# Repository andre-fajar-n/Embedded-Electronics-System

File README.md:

# Embedded Electronics System Lecture
This repo contains project - project about Embedded Electronics System Lecture when I was in college

## List Contents
### 1. [Circuit Design of AT89C51 and ATMega16](https://github.com/andre-fajar-n/embedded-electronics-system/tree/master/circuit_design)

### 2. [Firmware using Assembly Language](https://github.com/andre-fajar-n/embedded-electronics-system/tree/master/assembly_language)
In this language, there are 3 projects, such as: </br>
a. Showing text in LCD 16x2</br>
b. Automatic Water Reservoir</br>
c. Control Servo</br>

### 3. [Firmware using Bascom Language](https://github.com/andre-fajar-n/embedded-electronics-system/tree/master/bascom_language)
In this language, there are 2 projects, such as: </br>
a. Showing Counter in LCD 16x2</br>
b. Reading the tilt of device from MPU6050 and send Message to a phone number using SIM800L</br>

### 4. [Final Project for this lecture](https://github.com/andre-fajar-n/embedded-electronics-system/tree/master/pulse_position_modulation)
The purpose of final project was sent the signal from one microcontroller to another microcontroller by **PPM (Pulse Position Modulation)** method. The number of signal that was sent is 8 signals. The **sender** used **ATMega16** and the **receiver** used **Arduino Mega** To send the signal, I used infrared LED. And to receive the signal, I used photodiode.

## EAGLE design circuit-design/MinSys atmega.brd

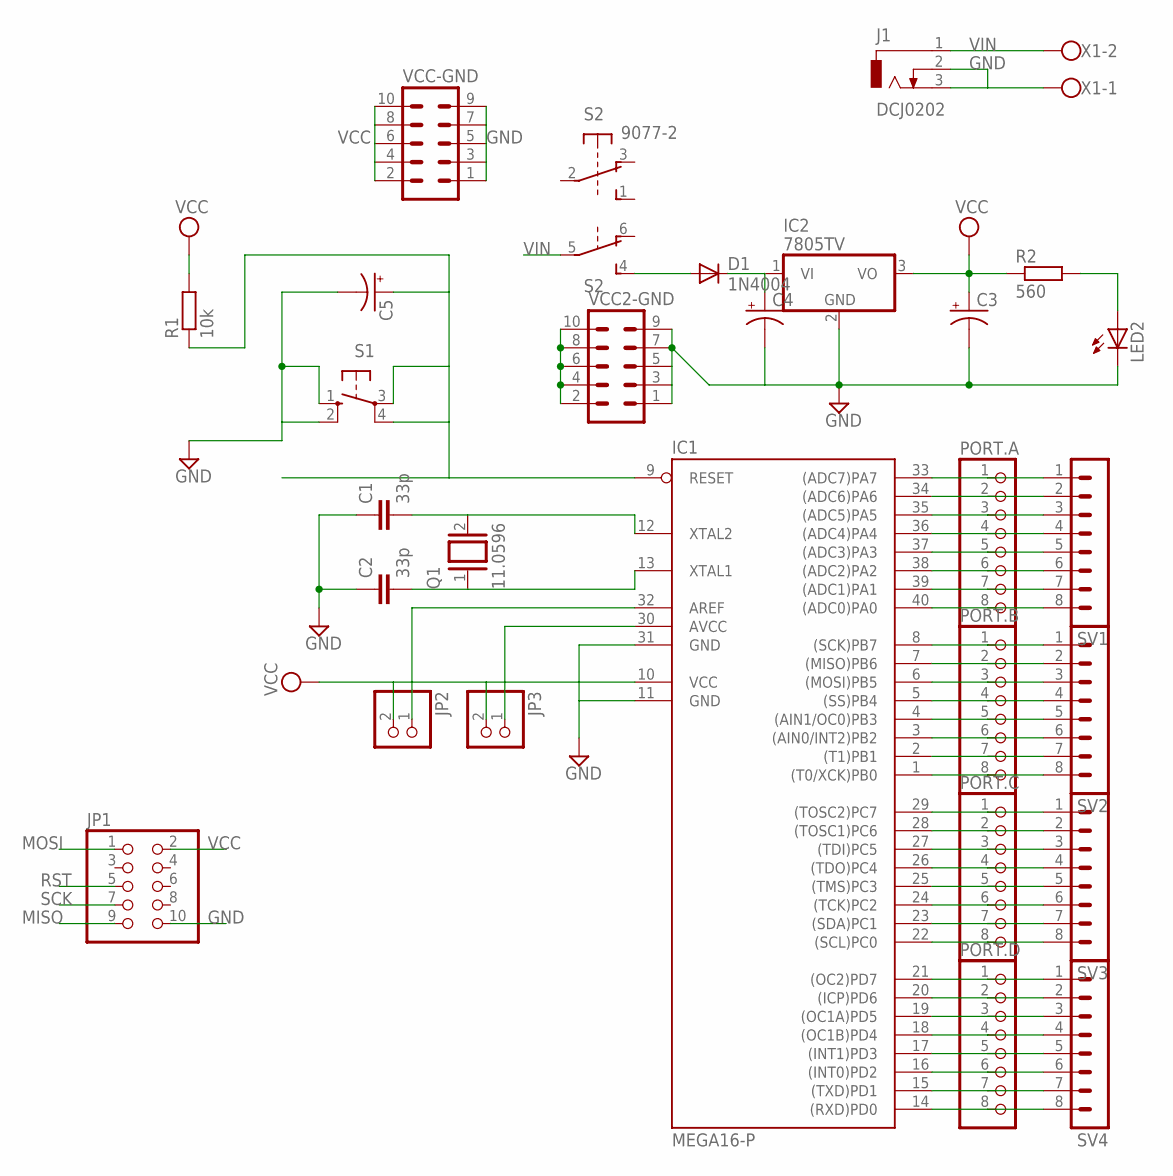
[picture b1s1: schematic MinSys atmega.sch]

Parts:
C1, C2: 33p; C2.5-3
C3, C4: CPOL-USE2,5-6E; E2,5-6E
C5: CPOL-USE2.5-6; E2,5-6
D1: 1N4004; DO41-10
IC1: MEGA16-P; DIL40
IC2: 7805TV; TO220V
J1: DCJ0202
JP1: PINHD-2X5; 2X05
JP2, JP3: PINHD-1X2; 1X02
LED2: LED3MM
PORT.A, PORT.B, PORT.C, PORT.D: PINHD-1X8; 1X08
Q1: 11.0596; QS
R1: 10k; 0207/10
R2: 560; 0207/10
S1: 10-XX; B3F-10XX
S2: 9077-2
SV1, SV2, SV3, SV4: MA08-1
VCC2-GND: MA05-2
VCC-GND: MA05-2
X1: W237-102

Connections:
GND: C1.1, C2.1, C3.-, C4.-, C5.-, IC1.11 (GND), IC1.31 (GND), IC2.2 (GND), J1.2, J1.3, JP1.10, LED2.K (C), S1.1 (S), S1.2 (S1), VCC2-GND.1, VCC2-GND.3, VCC2-GND.5, VCC2-GND.7, VCC2-GND.9, VCC-GND.1, VCC-GND.3, VCC-GND.5, VCC-GND.7, VCC-GND.9, X1.1
MISO: IC1.7 ((MISO)PB6), JP1.9, PORT.B.2, SV2.2
MOSI: IC1.6 ((MOSI)PB5), JP1.1, PORT.B.3, SV2.3
unnamed: IC1.33 ((ADC7)PA7), PORT.A.1, SV1.1
unnamed: D1.A, S2.4 (S)
unnamed: IC1.34 ((ADC6)PA6), PORT.A.2, SV1.2
unnamed: IC1.32 (AREF), JP2.1
unnamed: IC1.30 (AVCC), JP3.1
unnamed: C1.2, IC1.12 (XTAL2), Q1.2
unnamed: C2.2, IC1.13 (XTAL1), Q1.1
unnamed: C4.+, D1.C, IC2.1 (VI)
unnamed: LED2.A, R2.2
P02: IC1.35 ((ADC5)PA5), PORT.A.3, SV1.3
P03: IC1.36 ((ADC4)PA4), PORT.A.4, SV1.4
P04: IC1.37 ((ADC3)PA3), PORT.A.5, SV1.5
P05: IC1.38 ((ADC2)PA2), PORT.A.6, SV1.6
P06: IC1.39 ((ADC1)PA1), PORT.A.7, SV1.7
P07: IC1.40 ((ADC0)PA0), PORT.A.8, SV1.8
P10: IC1.14 ((RXD)PD0), PORT.D.8, SV4.8
P11: IC1.15 ((TXD)PD1), PORT.D.7, SV4.7
P12: IC1.16 ((INT0)PD2), PORT.D.6, SV4.6
P13: IC1.17 ((INT1)PD3), PORT.D.5, SV4.5
P14: IC1.18 ((OC1B)PD4), PORT.D.4, SV4.4
P15: IC1.19 ((OC1A)PD5), PORT.D.3, SV4.3
P16: IC1.20 ((ICP)PD6), PORT.D.2, SV4.2
P17: IC1.21 ((OC2)PD7), PORT.D.1, SV4.1
P23: IC1.5 ((SS)PB4), PORT.B.4, SV2.4
P24: IC1.4 ((AIN1/OC0)PB3), PORT.B.5, SV2.5
P25: IC1.3 ((AIN0/INT2)PB2), PORT.B.6, SV2.6
P26: IC1.2 ((T1)PB1), PORT.B.7, SV2.7
P27: IC1.1 ((T0/XCK)PB0), PORT.B.8, SV2.8
P30: IC1.22 ((SCL)PC0), PORT.C.8, SV3.8
P31: IC1.23 ((SDA)PC1), PORT.C.7, SV3.7
P32: IC1.24 ((TCK)PC2), PORT.C.6, SV3.6
P33: IC1.25 ((TMS)PC3), PORT.C.5, SV3.5
P34: IC1.26 ((TDO)PC4), PORT.C.4, SV3.4
P35: IC1.27 ((TDI)PC5), PORT.C.3, SV3.3
P36: IC1.28 ((TOSC1)PC6), PORT.C.2, SV3.2
P37: IC1.29 ((TOSC2)PC7), PORT.C.1, SV3.1
RST: C5.+, IC1.9 (RESET), JP1.5, R1.1, S1.3, S1.4 (P1)
SCK: IC1.8 ((SCK)PB7), JP1.7, PORT.B.1, SV2.1
VCC: C3.+, IC1.10 (VCC), IC2.3 (VO), JP1.2, JP2.2, JP3.2, R1.2, R2.1, VCC2-GND.2, VCC2-GND.4, VCC2-GND.6, VCC2-GND.8, VCC2-GND.10, VCC-GND.2, VCC-GND.4, VCC-GND.6, VCC-GND.8, VCC-GND.10
VIN: J1.1, S2.5, X1.2

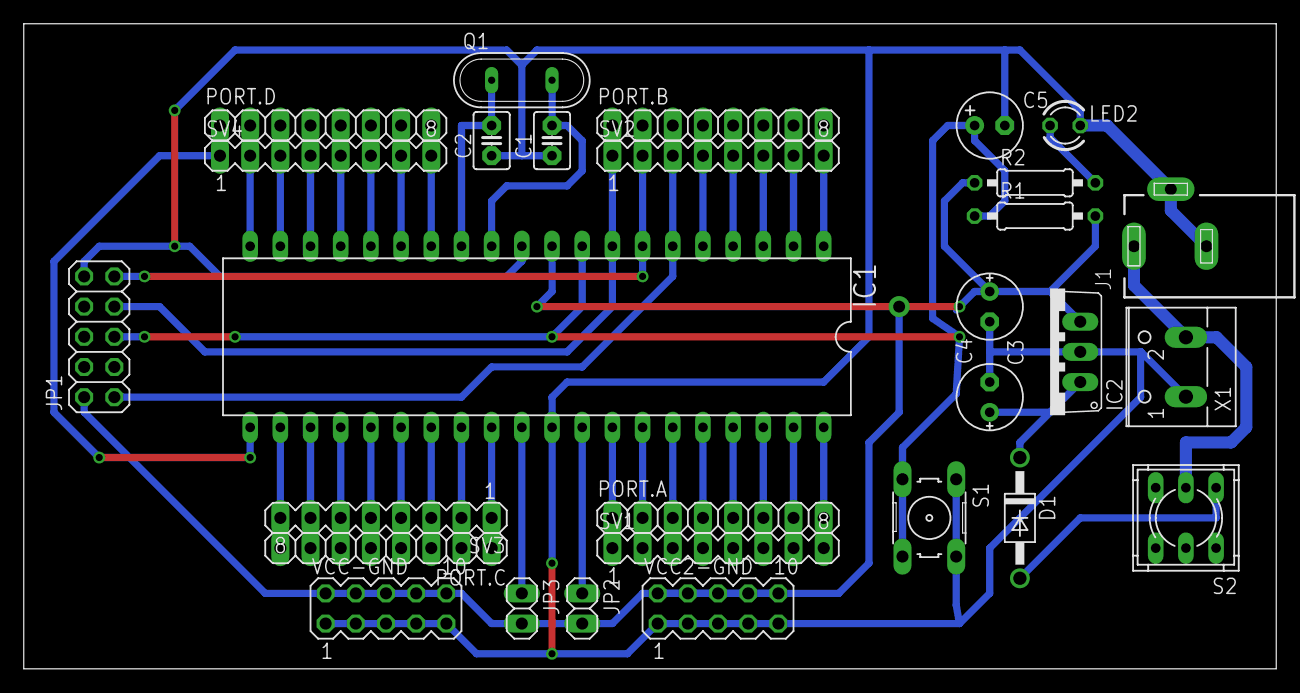
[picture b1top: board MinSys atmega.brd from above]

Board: 2 copper layers, 105.4 x 54.3 mm, 29 parts (0 on the bottom side), 43 nets.

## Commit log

2020-10-01 add pcb design
2020-10-01 init project PPM
2020-10-01 update project PPM and add readme
2020-10-01 change filename receiver
2020-10-01 init water reservoir and others change
2020-10-01 init project bascom
2020-10-01 init control servo with assembly and create folder assembly language
2020-10-01 restructurisation folder bascom
2020-10-01 restructurisation folder assembly
2020-10-01 edit readme bascom
2020-10-01 add LCD with assembly
2020-10-02 edit bascom MPU6050
2020-10-18 add picture of circuit design
2020-10-27 edit text to bold
